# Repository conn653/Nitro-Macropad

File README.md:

# Nitro-Macropad

## Overview
The Nitro-Macropad is a 9-key mechanical macro pad with a rotary encoder and an OLED display, powered by the Seeed XIAO RP2040. Designed in KiCad and running on KMK Firmware. The 9 keys are arranged in a 3x3 grid.

| Full Case | Case Apart |
| :---: | :---: |
|  |  |

| PCB | Schematic |
| :---: | :---: |
|  |  |
## Features

* 9 Mechanical Keys (Cherry MX footprint)
* Rotary Encoder for volume/scrolling
* OLED Display (0.91" I2C)
* QMK/KMK Compatible

## Project Structure

* `/PCB`: KiCad schematic and PCB layout.
* `/Case`: 3D printable case files (STEP).
* `/Firmware`: KMK (CircuitPython) configuration code.
* `/Production`: Everything you need to replicate the Nitro-Macropad.

## Bill of Materials (BOM)
* 1x Seeed XIAO RP2040 (Microcontroller)
* 9x Cherry MX Style Switches 
* 9x 1N4148 Diodes (Through Hole) 
* 1x EC11 Rotary Encoder 
* 1x 0.91" OLED 
* Case 3D Printed (PLA/PETG) 

## Firmware Setup
1\.  Install \[CircuitPython](https://circuitpython.org/board/seeeduino\_xiao\_rp2040/) on the XIAO.
2\.  Copy the \[KMK Firmware](https://github.com/KMKfw/kmk\_firmware) library to the board.
3\.  Copy `Main.py` from the `/Production` folder to the root of the device.

## License
This project is open source. Feel free to use and modify!

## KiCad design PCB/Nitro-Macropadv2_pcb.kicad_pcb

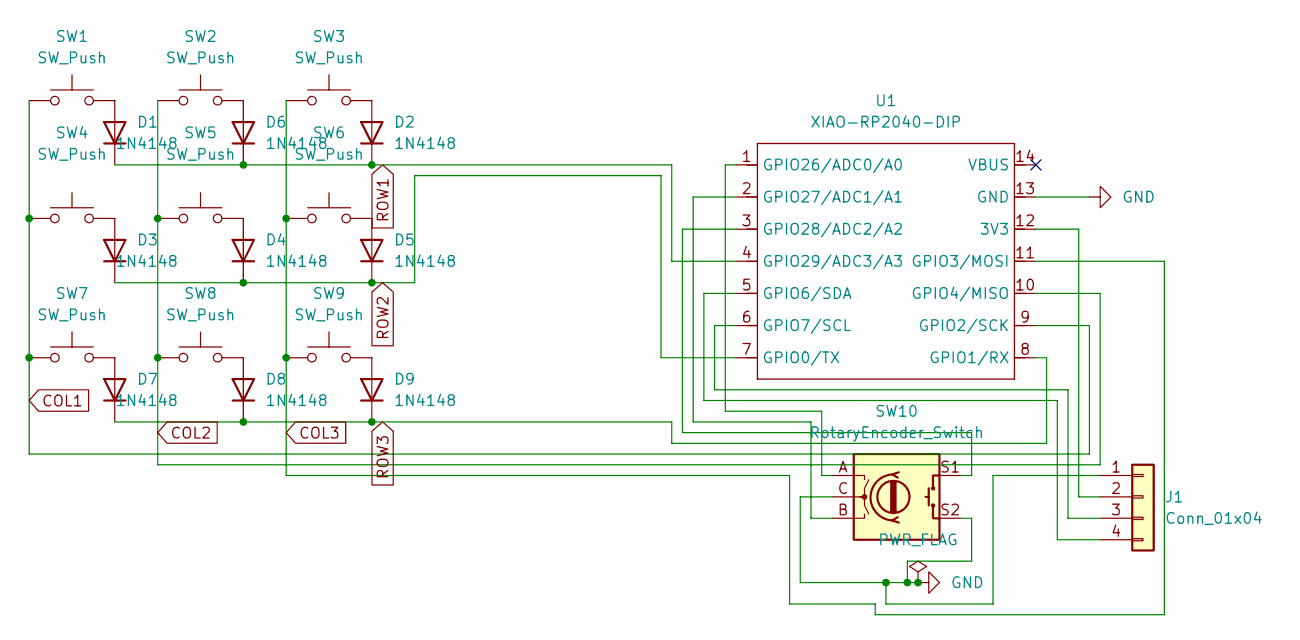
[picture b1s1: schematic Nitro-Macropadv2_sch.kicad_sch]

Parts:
D1, D2, D3, D4, D5, D6, D7, D8, D9: 1N4148; D_DO-35_SOD27_P7.62mm_Horizontal
J1: Conn_01x04; PinSocket_1x04_P2.54mm_Vertical
SW1, SW2, SW3, SW4, SW5, SW6, SW7, SW8, SW9: SW_Push; SW_Cherry_MX_1.00u_PCB
SW10: RotaryEncoder_Switch; RotaryEncoder_Alps_EC11E-Switch_Vertical_H20mm
U1: XIAO-RP2040-DIP

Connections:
COL1: SW1.1, SW4.1, SW7.1, U1.9 (GPIO2/SCK)
COL2: SW2.1, SW5.1, SW8.1, U1.10 (GPIO4/MISO)
COL3: SW3.1, SW6.1, SW9.1, U1.11 (GPIO3/MOSI)
GND: J1.1, SW10.C, SW10.S2, U1.13 (GND)
unnamed: D1.2 (A), SW1.2
unnamed: D2.2 (A), SW3.2
unnamed: D3.2 (A), SW4.2
unnamed: D4.2 (A), SW5.2
unnamed: D5.2 (A), SW6.2
unnamed: D6.2 (A), SW2.2
unnamed: D7.2 (A), SW7.2
unnamed: D8.2 (A), SW8.2
unnamed: D9.2 (A), SW9.2
unnamed: J1.2, U1.12 (3V3)
unnamed: J1.3, U1.6 (GPIO7/SCL)
unnamed: J1.4, U1.5 (GPIO6/SDA)
unnamed: SW10.A, U1.1 (GPIO26/ADC0/A0)
unnamed: SW10.B, U1.2 (GPIO27/ADC1/A1)
unnamed: SW10.S1, U1.3 (GPIO28/ADC2/A2)
ROW1: D1.1 (K), D2.1 (K), D6.1 (K), U1.4 (GPIO29/ADC3/A3)
ROW2: D3.1 (K), D4.1 (K), D5.1 (K), U1.7 (GPIO0/TX)
ROW3: D7.1 (K), D8.1 (K), D9.1 (K), U1.8 (GPIO1/RX)

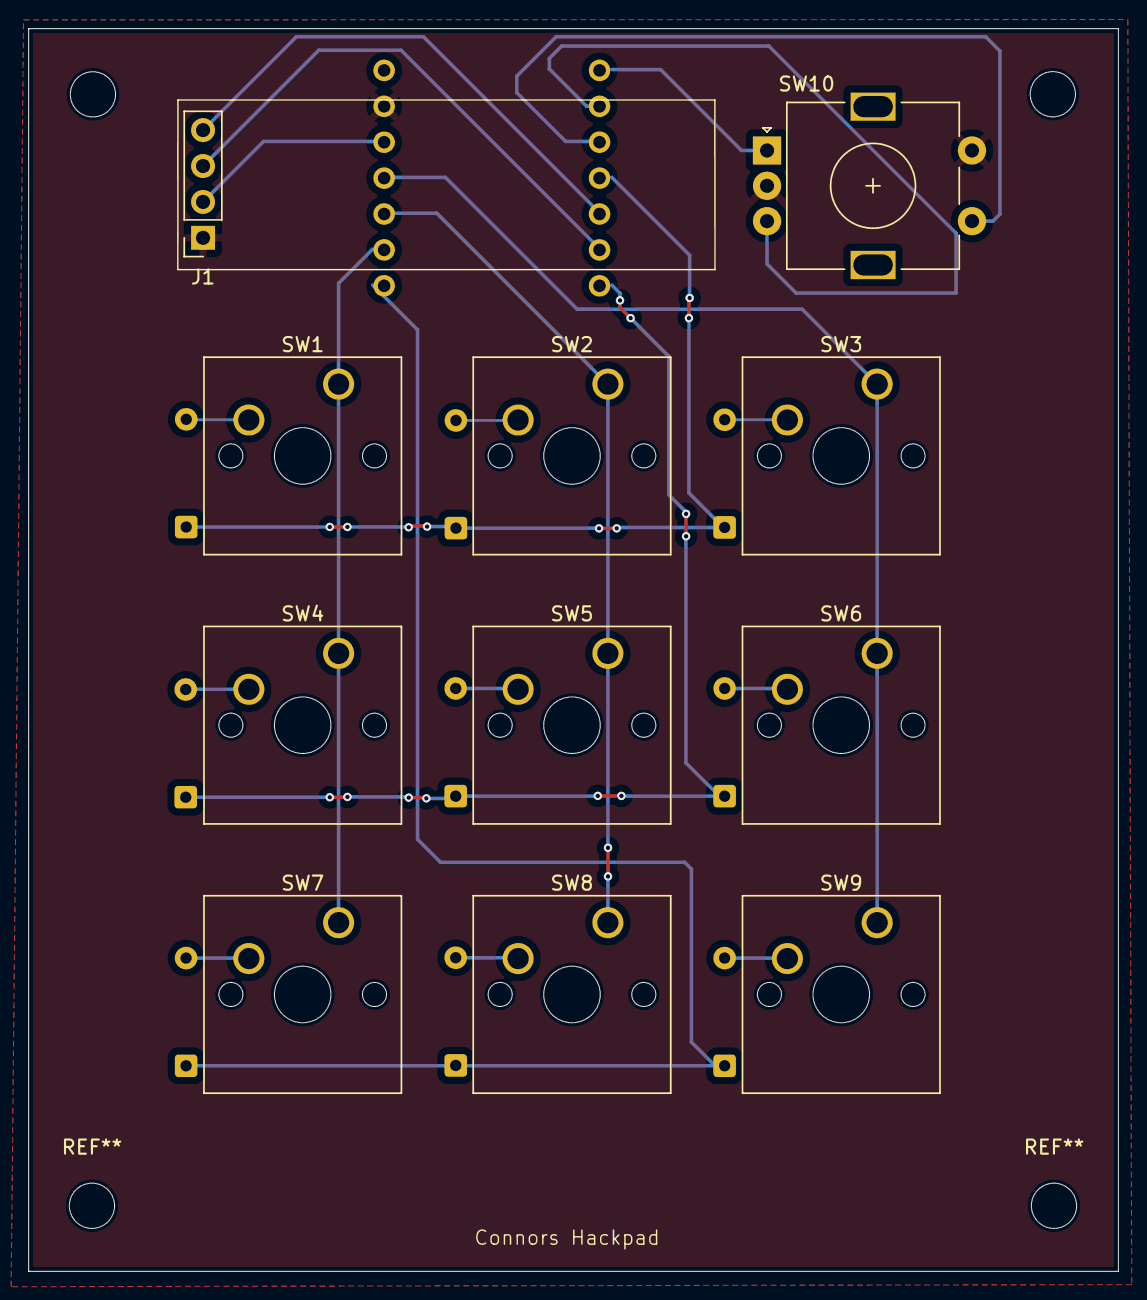
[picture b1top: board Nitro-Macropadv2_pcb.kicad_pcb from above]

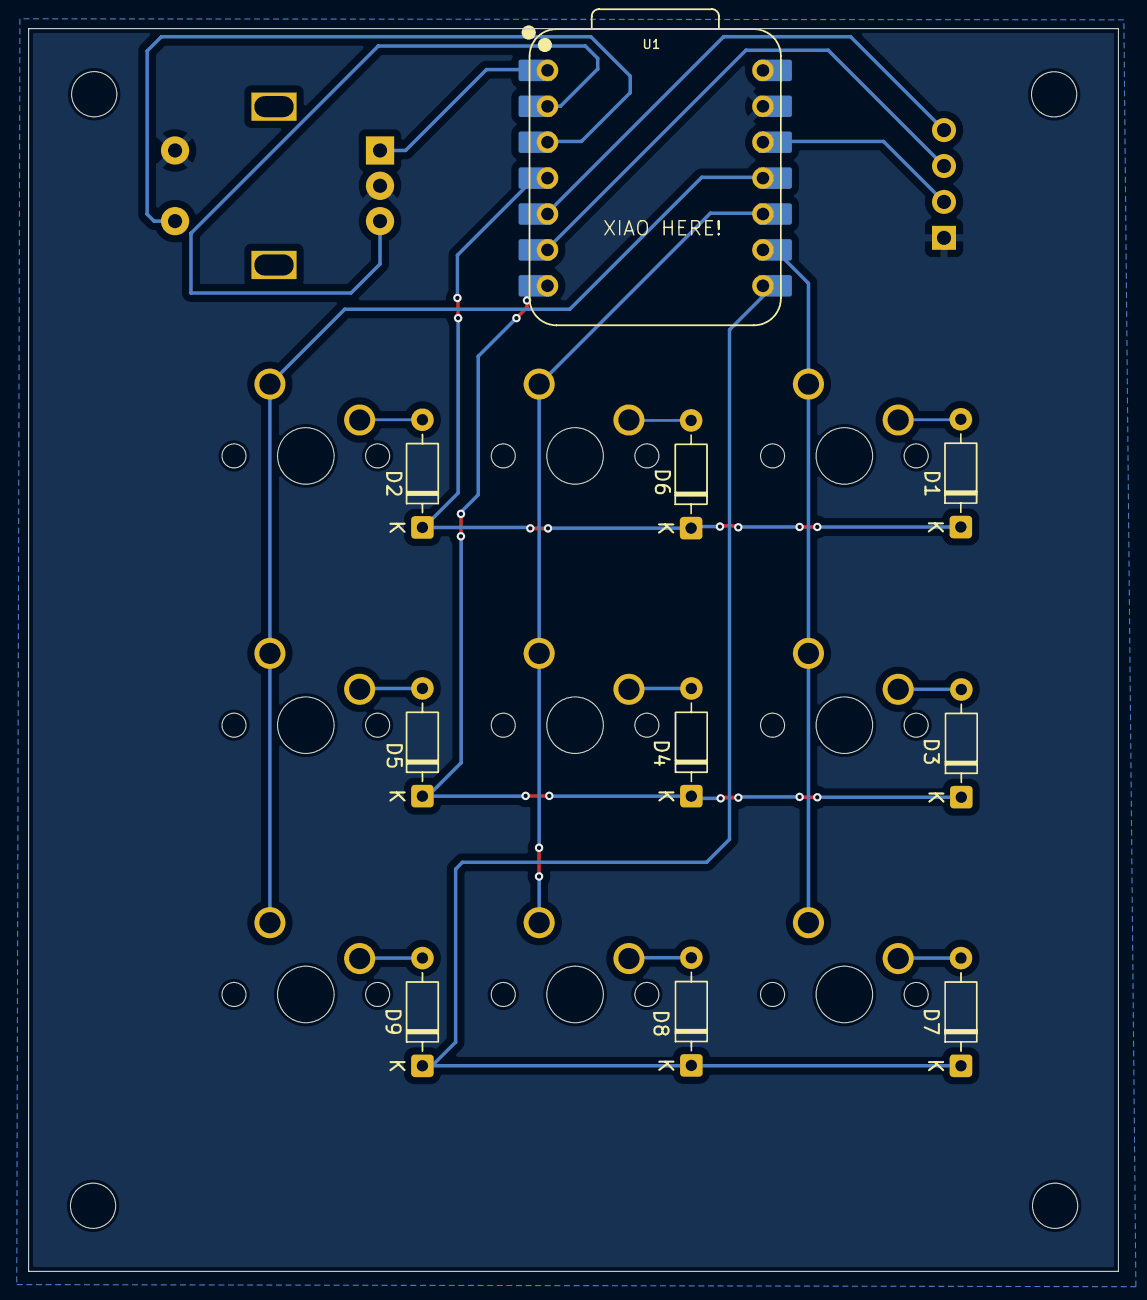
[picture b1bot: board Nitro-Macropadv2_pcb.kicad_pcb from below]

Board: 2 copper layers, 77.1 x 87.9 mm, 21 parts (10 on the bottom side), 22 nets.

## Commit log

2025-12-23 Initial release: PCB, Case, Production and Firmware
2025-12-23 Fixed images and renamed files
